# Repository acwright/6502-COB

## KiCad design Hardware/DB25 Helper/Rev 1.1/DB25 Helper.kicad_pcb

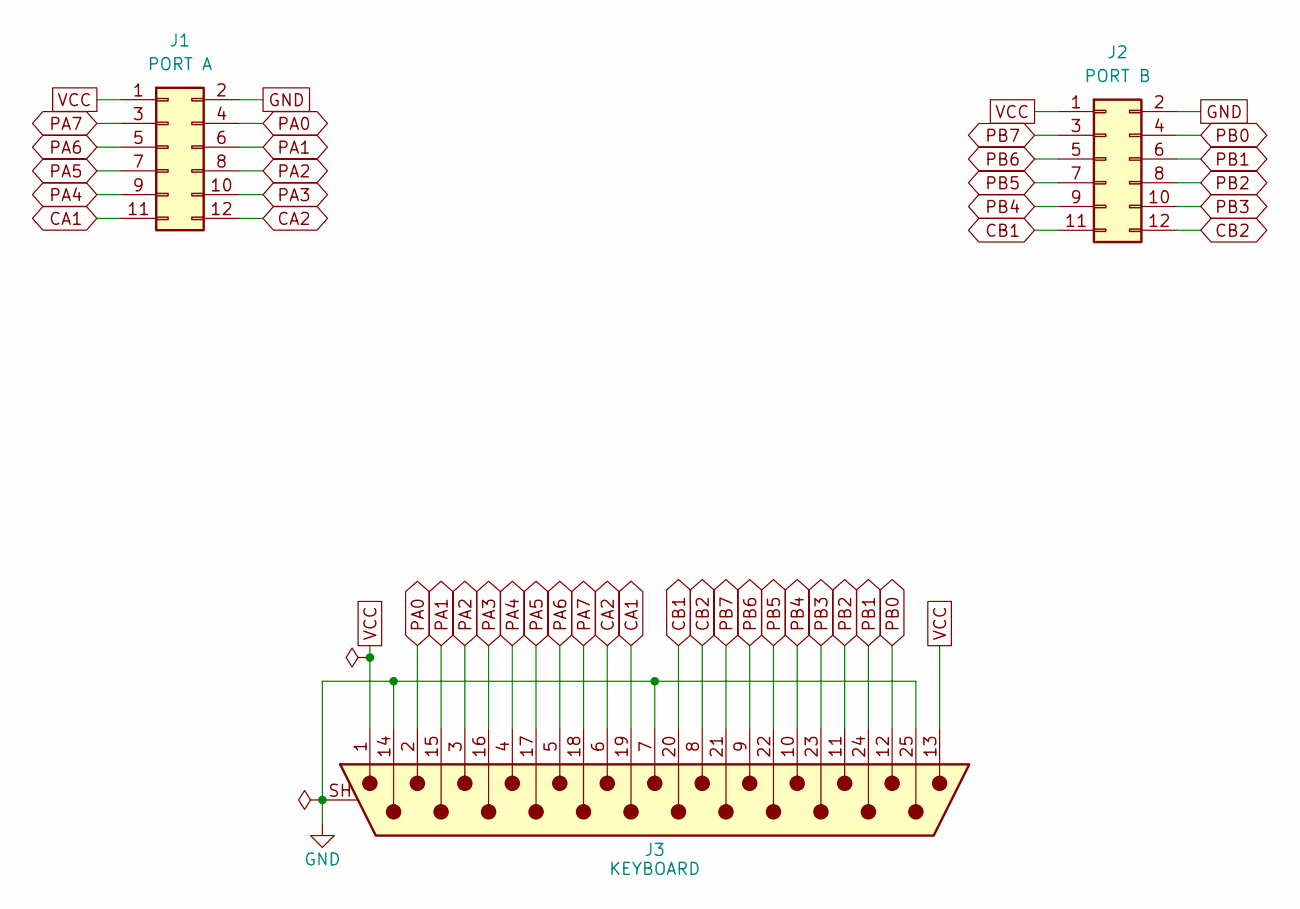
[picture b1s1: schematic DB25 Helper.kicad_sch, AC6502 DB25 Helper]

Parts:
J1: PORT A; 6502 GPIO Connector; Digikey 2057-BHR-12-VUA-ND
J2: PORT B; 6502 GPIO Connector; Digikey 2057-BHR-12-VUA-ND
J3: KEYBOARD; DSUB-25_Pins_Horizontal_P2.77x2.84mm_EdgePinOffset7.70mm_Ho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; Digikey 609-1505-ND

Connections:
CA1: J1.11, J3.19
CA2: J1.12, J3.6
CB1: J2.11, J3.20
CB2: J2.12, J3.8
GND: J1.2, J2.2, J3.7, J3.14, J3.25, J3.SH (PAD)
PA0: J1.4, J3.2
PA1: J1.6, J3.15
PA2: J1.8, J3.3
PA3: J1.10, J3.16
PA4: J1.9, J3.4
PA5: J1.7, J3.17
PA6: J1.5, J3.5
PA7: J1.3, J3.18
PB0: J2.4, J3.12
PB1: J2.6, J3.24
PB2: J2.8, J3.11
PB3: J2.10, J3.23
PB4: J2.9, J3.10
PB5: J2.7, J3.22
PB6: J2.5, J3.9
PB7: J2.3, J3.21
VCC: J1.1, J2.1, J3.1, J3.13

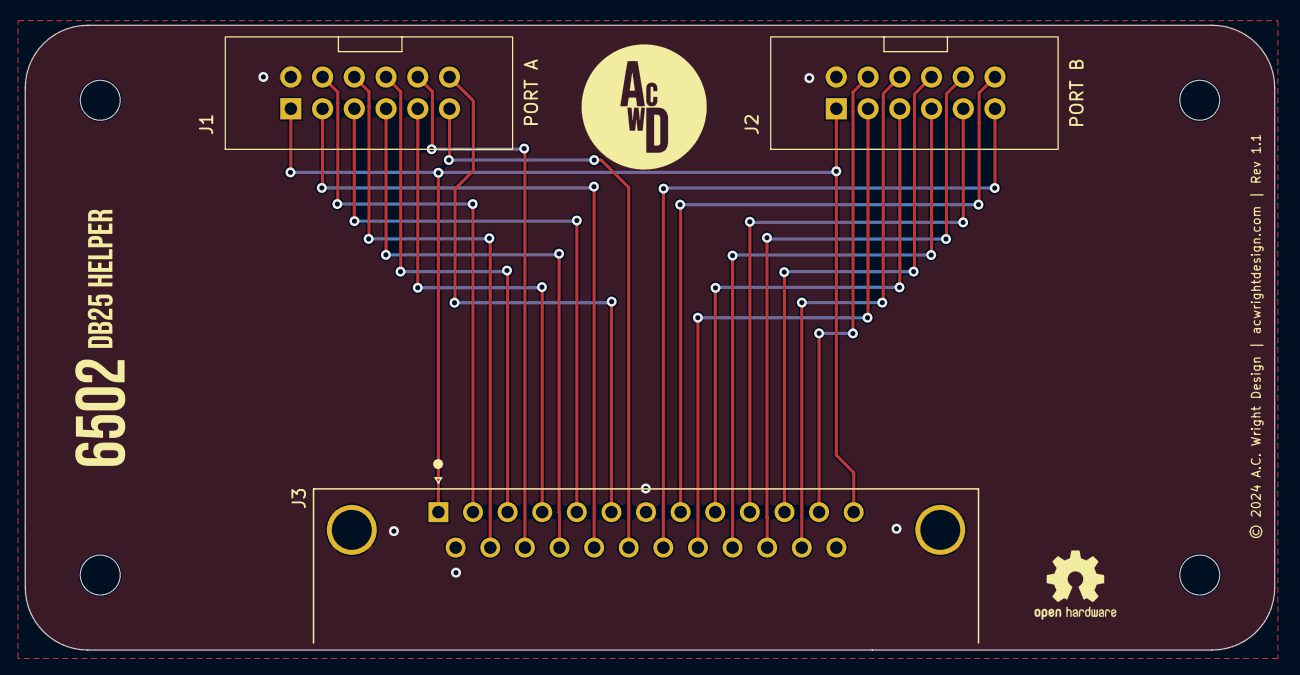
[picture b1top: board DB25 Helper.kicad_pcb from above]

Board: 2 copper layers, 100.0 x 50.0 mm, 7 parts (0 on the bottom side), 22 nets.

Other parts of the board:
H1, H2, H3, H4: MountingHole; MountingHole_3.2mm_M3

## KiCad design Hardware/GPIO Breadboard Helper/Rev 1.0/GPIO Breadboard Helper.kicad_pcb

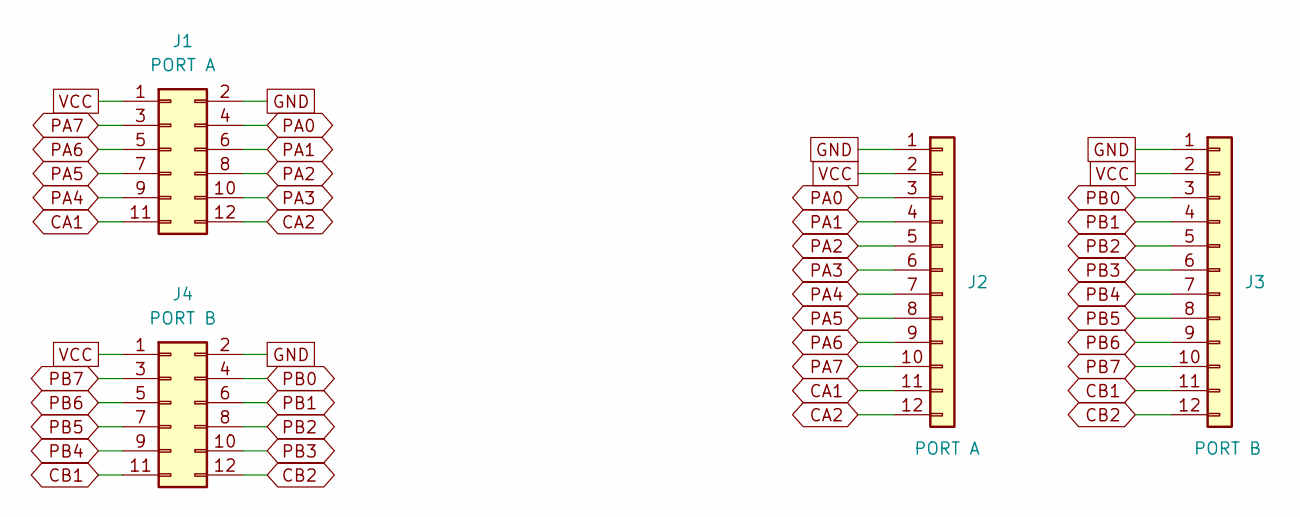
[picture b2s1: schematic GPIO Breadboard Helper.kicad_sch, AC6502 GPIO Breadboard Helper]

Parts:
J1: PORT A; 6502 GPIO Connector; Digikey 2057-BHR-12-VUA-ND
J2: PORT A; PinHeader_1x12_P2.54mm_Vertical; Digikey S1011EC-40-ND
J3: PORT B; PinHeader_1x12_P2.54mm_Vertical; Digikey S1011EC-40-ND
J4: PORT B; 6502 GPIO Connector; Digikey 2057-BHR-12-VUA-ND

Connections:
CA1: J1.11, J2.11
CA2: J1.12, J2.12
CB1: J3.11, J4.11
CB2: J3.12, J4.12
GND: J1.2, J2.1, J3.1, J4.2
PA0: J1.4, J2.3
PA1: J1.6, J2.4
PA2: J1.8, J2.5
PA3: J1.10, J2.6
PA4: J1.9, J2.7
PA5: J1.7, J2.8
PA6: J1.5, J2.9
PA7: J1.3, J2.10
PB0: J3.3, J4.4
PB1: J3.4, J4.6
PB2: J3.5, J4.8
PB3: J3.6, J4.10
PB4: J3.7, J4.9
PB5: J3.8, J4.7
PB6: J3.9, J4.5
PB7: J3.10, J4.3
VCC: J1.1, J2.2, J3.2, J4.1

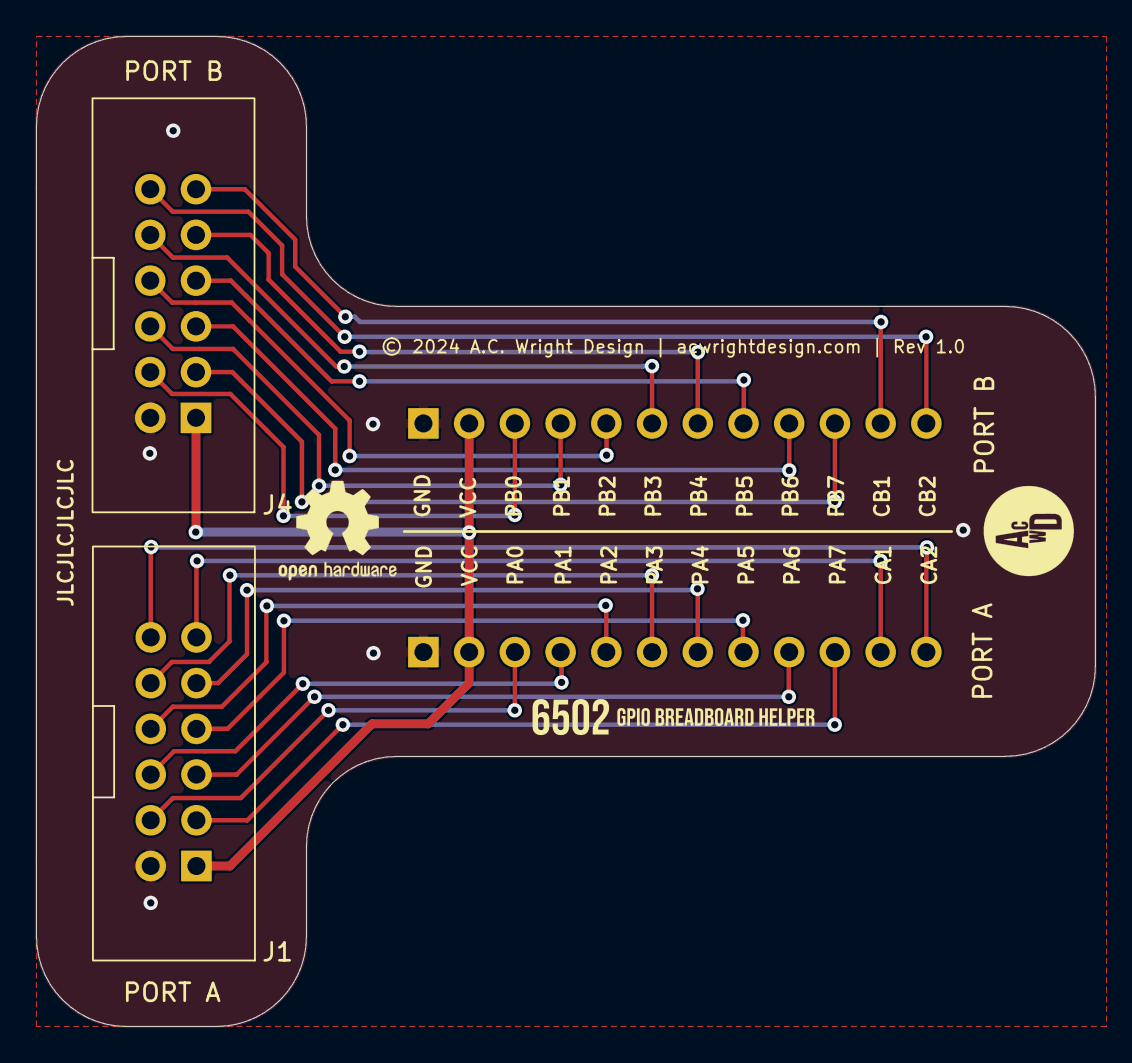
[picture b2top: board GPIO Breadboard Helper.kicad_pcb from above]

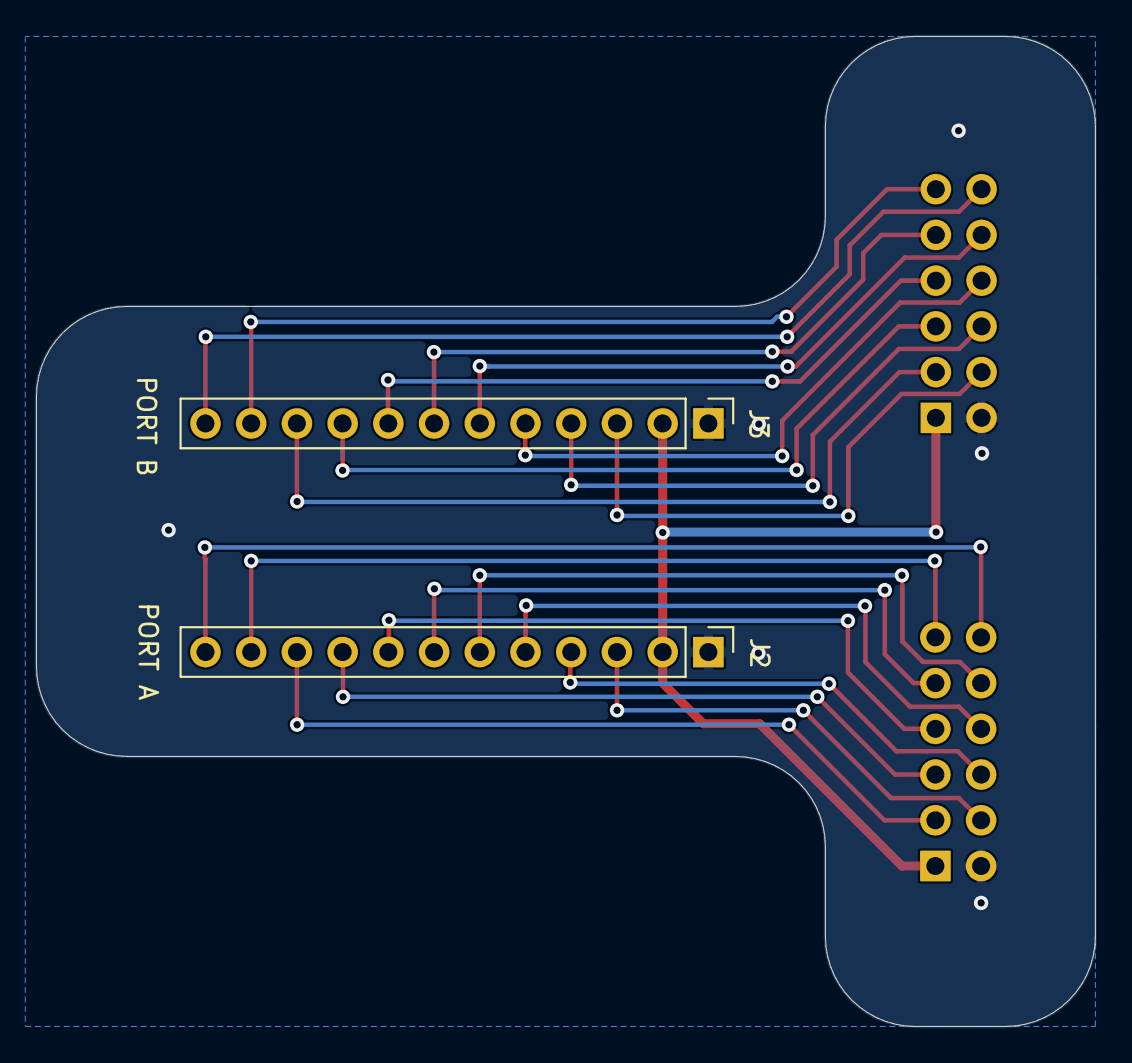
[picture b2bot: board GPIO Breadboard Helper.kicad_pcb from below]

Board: 2 copper layers, 58.8 x 55.0 mm, 4 parts (2 on the bottom side), 22 nets.

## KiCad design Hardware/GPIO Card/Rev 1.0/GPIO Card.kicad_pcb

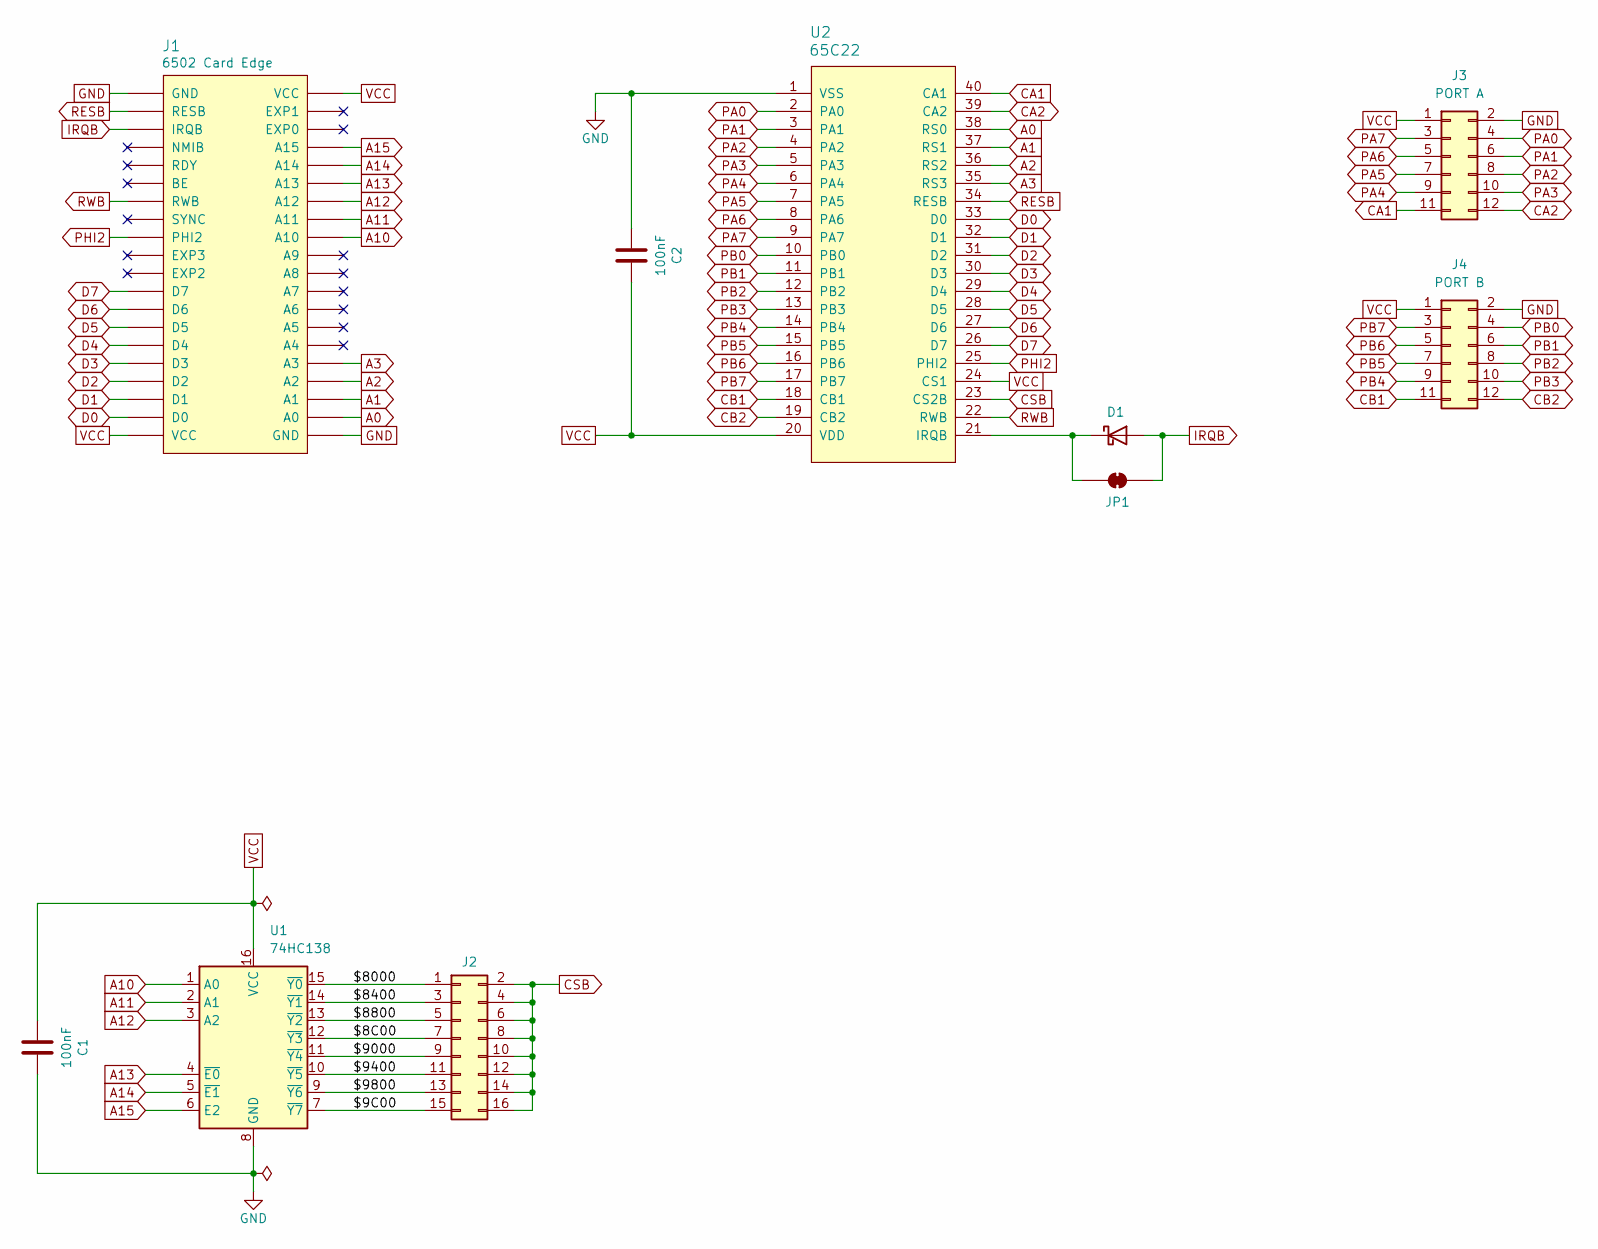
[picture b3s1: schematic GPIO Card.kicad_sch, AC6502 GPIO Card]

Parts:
C1, C2: 100nF; C_0805_2012Metric; LCSC C49678
D1: BAT85; D_DO-35_SOD27_P7.62mm_Horizontal; Digikey BAT85SCT-ND
J1: 6502 Card Edge
J2: Conn_02x08_Odd_Even; PinHeader_2x08_P2.54mm_Vertical; Digikey S2011EC-40-ND
J3: PORT A; 6502 GPIO Connector; Digikey 2057-BHR-12-VUA-ND
J4: PORT B; 6502 GPIO Connector; Digikey 2057-BHR-12-VUA-ND
JP1: SolderJumper_2_Bridged; SolderJumper-2_P1.3mm_Bridged_RoundedPad1.0x1.5mm
U1: 74HC138; SOIC-16_3.9x9.9mm_P1.27mm; LCSC C5602
U2: 65C22; DIP-40_W15.24mm_Socket_LongPads; Mouser 955-W65C22N6TPG-14

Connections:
/$8C00: J2.7, U1.12 (~Y3)
/$9C00: J2.15, U1.7 (~Y7)
/$8000: J2.1, U1.15 (~Y0)
/$8400: J2.3, U1.14 (~Y1)
/$8800: J2.5, U1.13 (~Y2)
/$9000: J2.9, U1.11 (~Y4)
/$9400: J2.11, U1.10 (~Y5)
/$9800: J2.13, U1.9 (~Y6)
A0: J1.A0, U2.38 (RS0)
A1: J1.A1, U2.37 (RS1)
A2: J1.A2, U2.36 (RS2)
A3: J1.A3, U2.35 (RS3)
A10: J1.A10, U1.1 (A0)
A11: J1.A11, U1.2 (A1)
A12: J1.A12, U1.3 (A2)
A13: J1.A13, U1.4 (~E0)
A14: J1.A14, U1.5 (~E1)
A15: J1.A15, U1.6 (E2)
CA1: J3.11, U2.40 (CA1)
CA2: J3.12, U2.39 (CA2)
CB1: J4.11, U2.18 (CB1)
CB2: J4.12, U2.19 (CB2)
CSB: J2.2, J2.4, J2.6, J2.8, J2.10, J2.12, J2.14, J2.16, U2.23 (CS2B)
D0: J1.D0, U2.33 (D0)
D1: J1.D1, U2.32 (D1)
D2: J1.D2, U2.31 (D2)
D3: J1.D3, U2.30 (D3)
D4: J1.D4, U2.29 (D4)
D5: J1.D5, U2.28 (D5)
D6: J1.D6, U2.27 (D6)
D7: J1.D7, U2.26 (D7)
GND: C1.2, C2.1, J1.GND, J3.2, J4.2, U1.8 (GND), U2.1 (VSS)
IRQB: D1.2 (A), J1.IRQB, JP1.2 (B)
unnamed: D1.1 (K), JP1.1 (A), U2.21 (IRQB)
PA0: J3.4, U2.2 (PA0)
PA1: J3.6, U2.3 (PA1)
PA2: J3.8, U2.4 (PA2)
PA3: J3.10, U2.5 (PA3)
PA4: J3.9, U2.6 (PA4)
PA5: J3.7, U2.7 (PA5)
PA6: J3.5, U2.8 (PA6)
PA7: J3.3, U2.9 (PA7)
PB0: J4.4, U2.10 (PB0)
PB1: J4.6, U2.11 (PB1)
PB2: J4.8, U2.12 (PB2)
PB3: J4.10, U2.13 (PB3)
PB4: J4.9, U2.14 (PB4)
PB5: J4.7, U2.15 (PB5)
PB6: J4.5, U2.16 (PB6)
PB7: J4.3, U2.17 (PB7)
PHI2: J1.PHI2, U2.25 (PHI2)
RESB: J1.RESB, U2.34 (RESB)
RWB: J1.RWB, U2.22 (RWB)
VCC: C1.1, C2.2, J1.VCC, J3.1, J4.1, U1.16 (VCC), U2.20 (VDD), U2.24 (CS1)

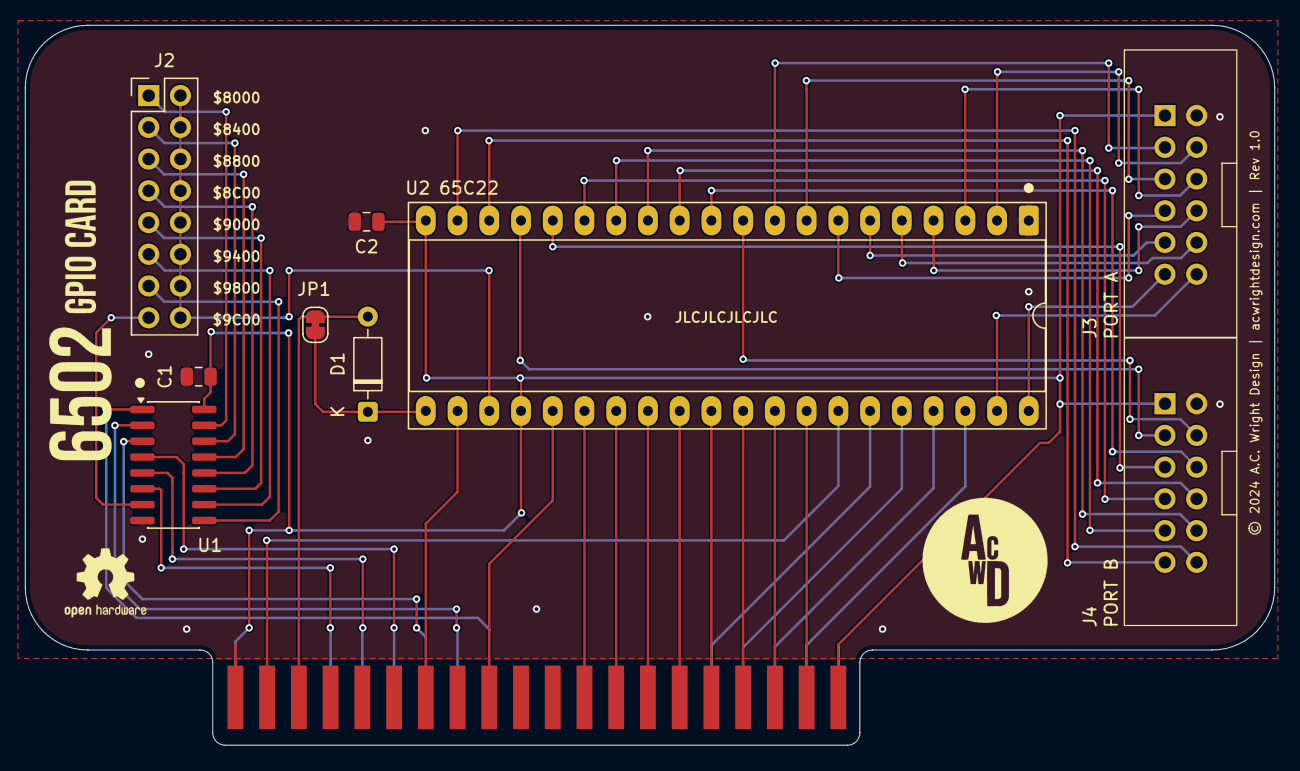
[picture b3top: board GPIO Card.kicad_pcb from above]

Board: 2 copper layers, 100.0 x 57.6 mm, 10 parts (0 on the bottom side), 54 nets.

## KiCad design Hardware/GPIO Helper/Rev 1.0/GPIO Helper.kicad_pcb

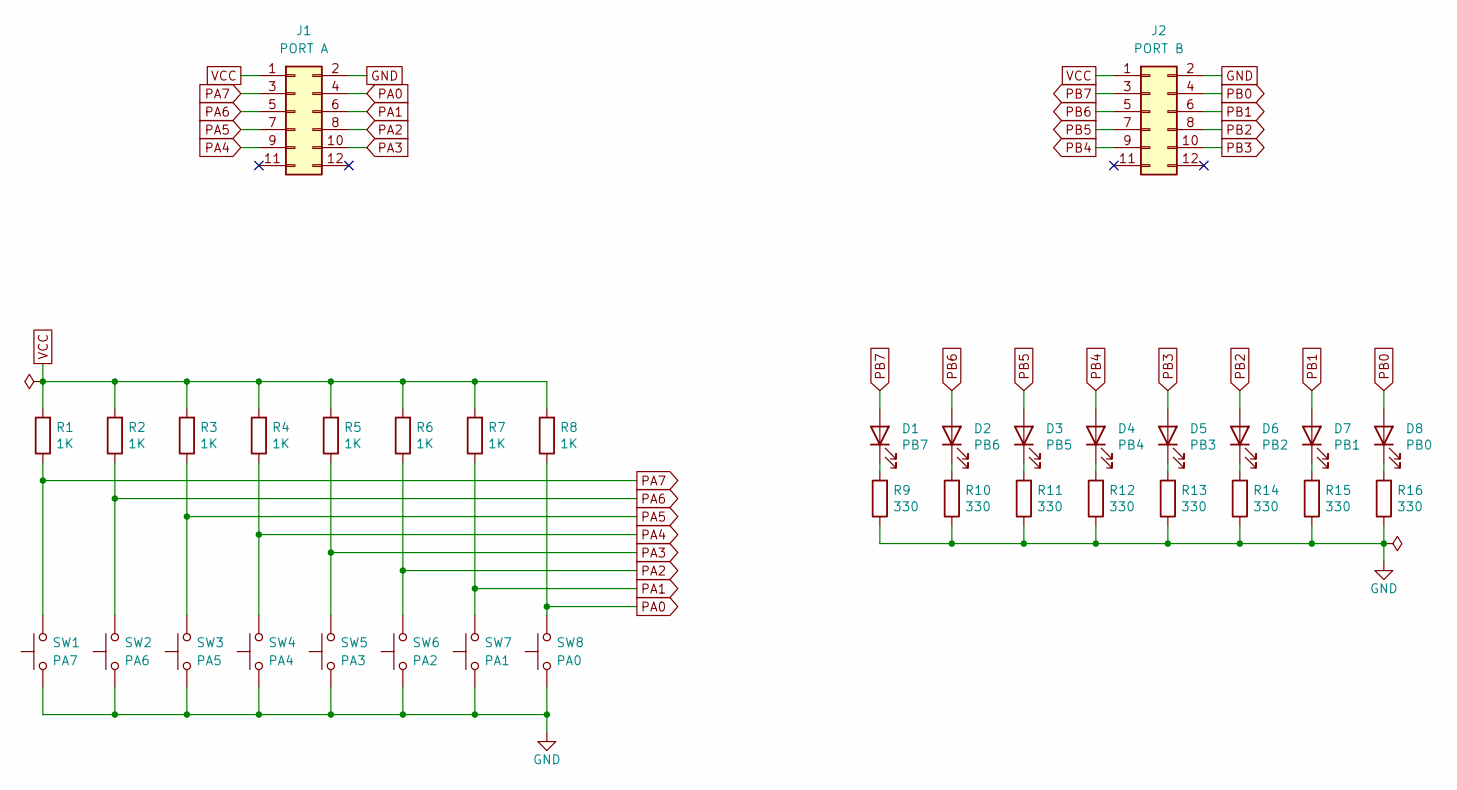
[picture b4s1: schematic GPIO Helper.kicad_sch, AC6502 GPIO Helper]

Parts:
D1: PB7; LED_D3.0mm; Digikey 732-5008-ND
D2: PB6; LED_D3.0mm; Digikey 732-5008-ND
D3: PB5; LED_D3.0mm; Digikey 732-5008-ND
D4: PB4; LED_D3.0mm; Digikey 732-5008-ND
D5: PB3; LED_D3.0mm; Digikey 732-5008-ND
D6: PB2; LED_D3.0mm; Digikey 732-5008-ND
D7: PB1; LED_D3.0mm; Digikey 732-5008-ND
D8: PB0; LED_D3.0mm; Digikey 732-5008-ND
J1: PORT A; 6502 GPIO Connector; Digikey 2057-BHR-12-VUA-ND
J2: PORT B; 6502 GPIO Connector; Digikey 2057-BHR-12-VUA-ND
R1, R2, R3, R4, R5, R6, R7, R8: 1K; R_Axial_DIN0204_L3.6mm_D1.6mm_P5.08mm_Horizontal; Digikey 13-MFR-12FTF52-1KCT-ND
R9, R10, R11, R12, R13, R14, R15, R16: 330; R_Axial_DIN0204_L3.6mm_D1.6mm_P5.08mm_Horizontal; Digikey 13-MFR-12FTF52-330RCT-ND
SW1: PA7; SW_PUSH_6mm; Digikey 2223-TS02-66-50-BK-160-LCR-D-ND
SW2: PA6; SW_PUSH_6mm; Digikey 2223-TS02-66-50-BK-160-LCR-D-ND
SW3: PA5; SW_PUSH_6mm; Digikey 2223-TS02-66-50-BK-160-LCR-D-ND
SW4: PA4; SW_PUSH_6mm; Digikey 2223-TS02-66-50-BK-160-LCR-D-ND
SW5: PA3; SW_PUSH_6mm; Digikey 2223-TS02-66-50-BK-160-LCR-D-ND
SW6: PA2; SW_PUSH_6mm; Digikey 2223-TS02-66-50-BK-160-LCR-D-ND
SW7: PA1; SW_PUSH_6mm; Digikey 2223-TS02-66-50-BK-160-LCR-D-ND
SW8: PA0; SW_PUSH_6mm; Digikey 2223-TS02-66-50-BK-160-LCR-D-ND

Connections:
GND: J1.2, J2.2, R9.1, R10.1, R11.1, R12.1, R13.1, R14.1, R15.1, R16.1, SW1.1, SW2.1, SW3.1, SW4.1, SW5.1, SW6.1, SW7.1, SW8.1
unnamed: D1.1 (K), R9.2
unnamed: D2.1 (K), R10.2
unnamed: D3.1 (K), R11.2
unnamed: D4.1 (K), R12.2
unnamed: D5.1 (K), R13.2
unnamed: D6.1 (K), R14.2
unnamed: D7.1 (K), R15.2
unnamed: D8.1 (K), R16.2
PA0: J1.4, R8.1, SW8.2
PA1: J1.6, R7.1, SW7.2
PA2: J1.8, R6.1, SW6.2
PA3: J1.10, R5.1, SW5.2
PA4: J1.9, R4.1, SW4.2
PA5: J1.7, R3.1, SW3.2
PA6: J1.5, R2.1, SW2.2
PA7: J1.3, R1.1, SW1.2
PB0: D8.2 (A), J2.4
PB1: D7.2 (A), J2.6
PB2: D6.2 (A), J2.8
PB3: D5.2 (A), J2.10
PB4: D4.2 (A), J2.9
PB5: D3.2 (A), J2.7
PB6: D2.2 (A), J2.5
PB7: D1.2 (A), J2.3
VCC: J1.1, J2.1, R1.2, R2.2, R3.2, R4.2, R5.2, R6.2, R7.2, R8.2

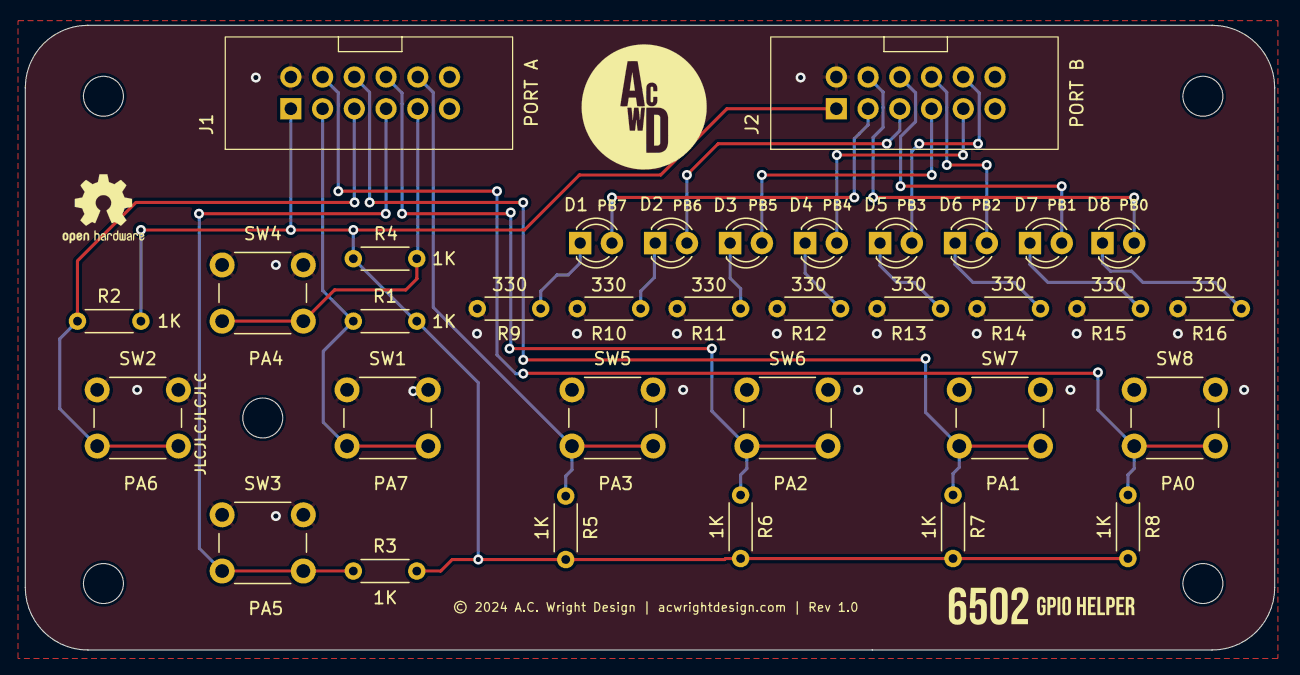
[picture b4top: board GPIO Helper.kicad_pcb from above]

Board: 2 copper layers, 100.0 x 50.0 mm, 39 parts (0 on the bottom side), 26 nets.

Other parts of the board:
H1, H2, H3, H4, H5: MountingHole; MountingHole_3.2mm_M3

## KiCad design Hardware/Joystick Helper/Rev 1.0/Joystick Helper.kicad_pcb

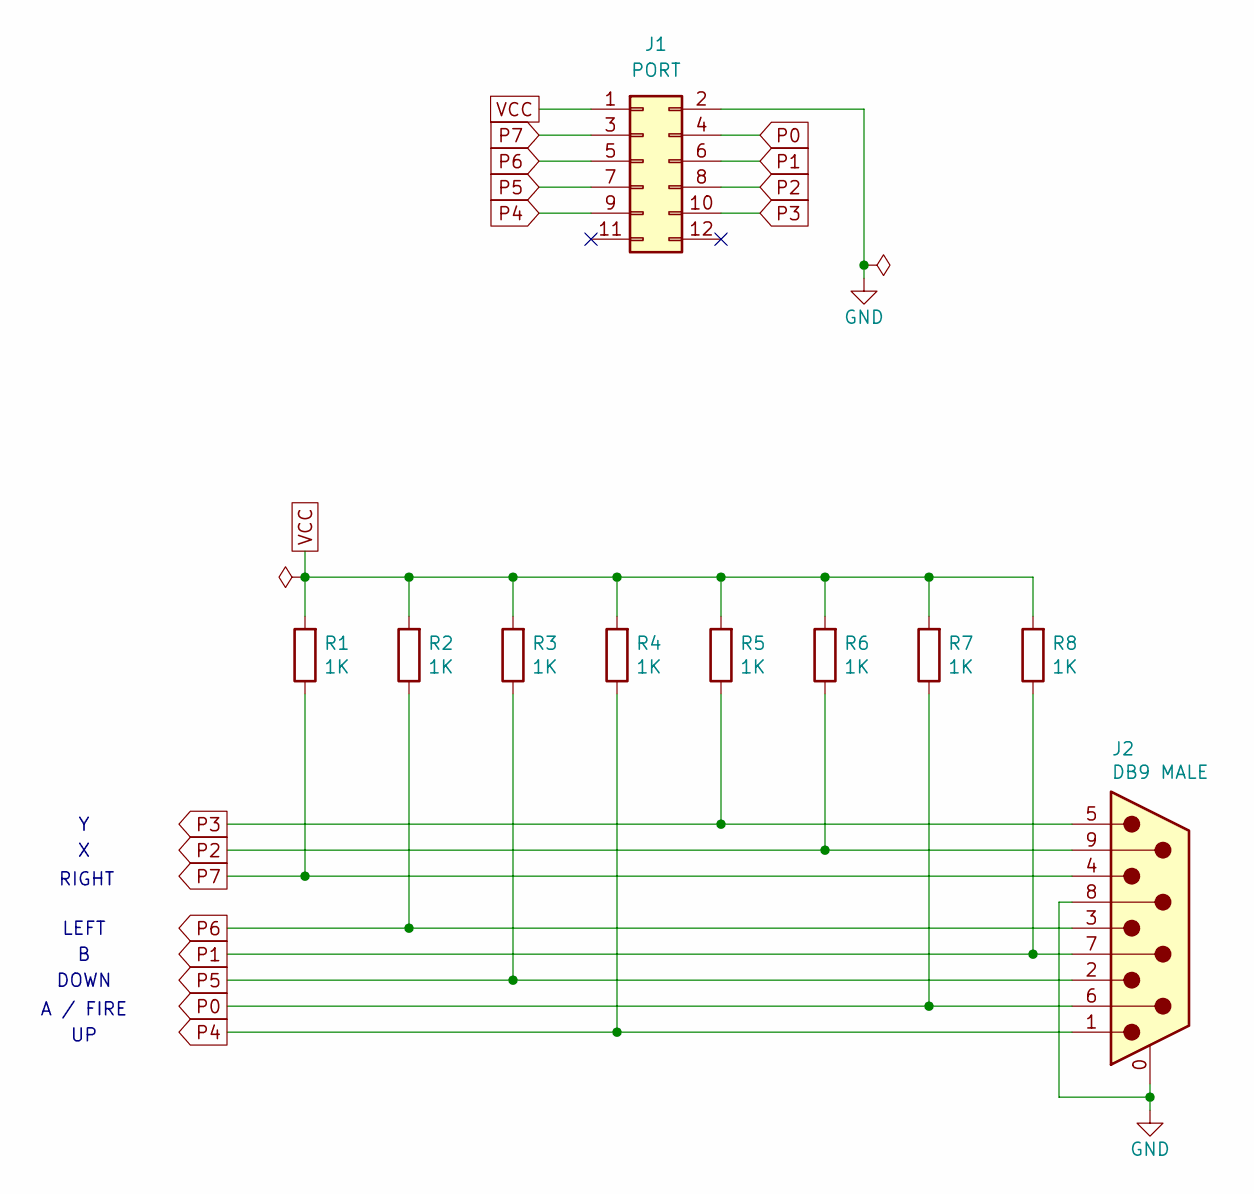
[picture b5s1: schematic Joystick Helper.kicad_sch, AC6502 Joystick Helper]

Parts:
J1: PORT; 6502 GPIO Connector; Digikey 2057-BHR-12-VUA-ND
J2: DB9 MALE; DSUB-9_Pins_Horizontal_P2.77x2.84mm_EdgePinOffset7.70mm_Hou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; Digikey 609-1481-ND
R1, R2, R3, R4, R5, R6, R7, R8: 1K; R_Axial_DIN0204_L3.6mm_D1.6mm_P5.08mm_Horizontal; Digikey 13-MFR-12FTF52-1KCT-ND

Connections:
GND: J1.2, J2.0 (PAD), J2.8
P0: J1.4, J2.6, R7.1
P1: J1.6, J2.7, R8.1
P2: J1.8, J2.9, R6.1
P3: J1.10, J2.5, R5.1
P4: J1.9, J2.1, R4.1
P5: J1.7, J2.2, R3.1
P6: J1.5, J2.3, R2.1
P7: J1.3, J2.4, R1.1
VCC: J1.1, R1.2, R2.2, R3.2, R4.2, R5.2, R6.2, R7.2, R8.2

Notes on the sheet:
LEFT
DOWN
RIGHT
A / FIRE

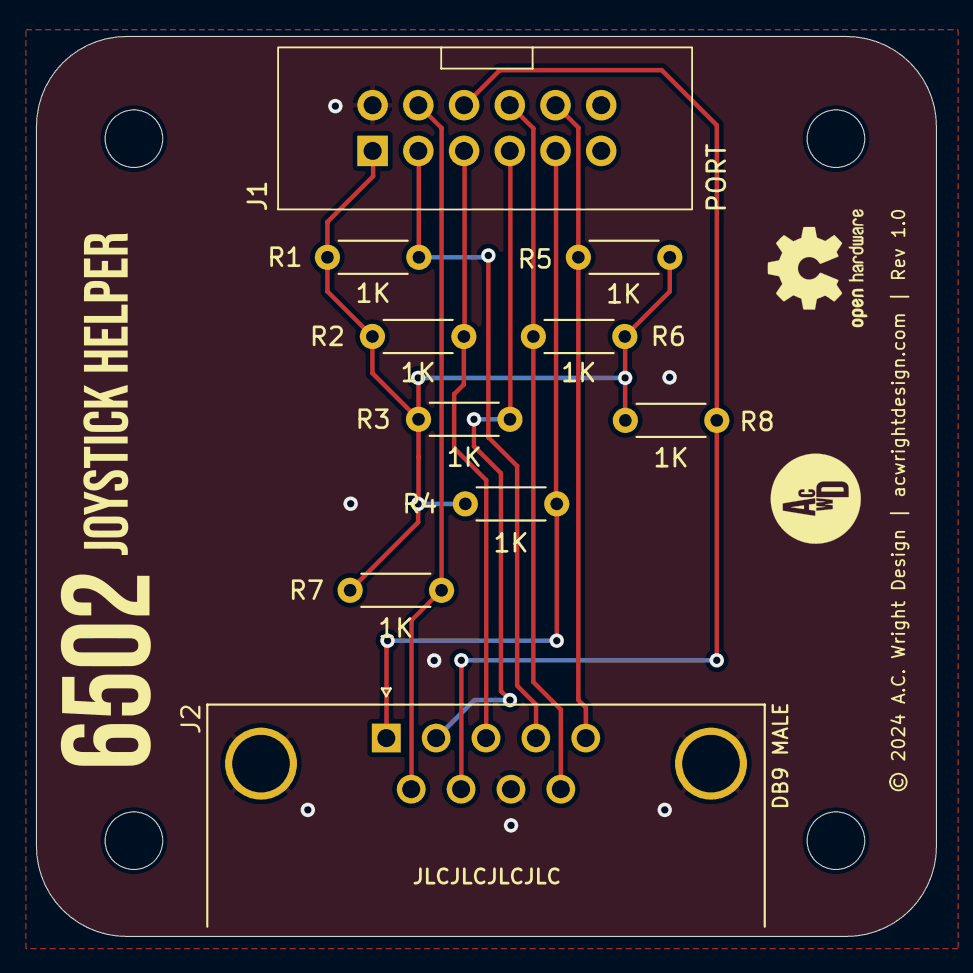
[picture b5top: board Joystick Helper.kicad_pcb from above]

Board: 2 copper layers, 50.0 x 50.0 mm, 14 parts (0 on the bottom side), 10 nets.

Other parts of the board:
H1, H2, H3, H4: MountingHole; MountingHole_3.2mm_M3

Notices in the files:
Hardware/DB25 Helper/Rev 1.1/DB25 Helper.kicad_pcb:
© 2024 A.C. Wright Design | acwrightdesign.com | Rev 1.1
Hardware/GPIO Breadboard Helper/Rev 1.0/GPIO Breadboard Helper.kicad_pcb:
© 2024 A.C. Wright Design | acwrightdesign.com | Rev 1.0
